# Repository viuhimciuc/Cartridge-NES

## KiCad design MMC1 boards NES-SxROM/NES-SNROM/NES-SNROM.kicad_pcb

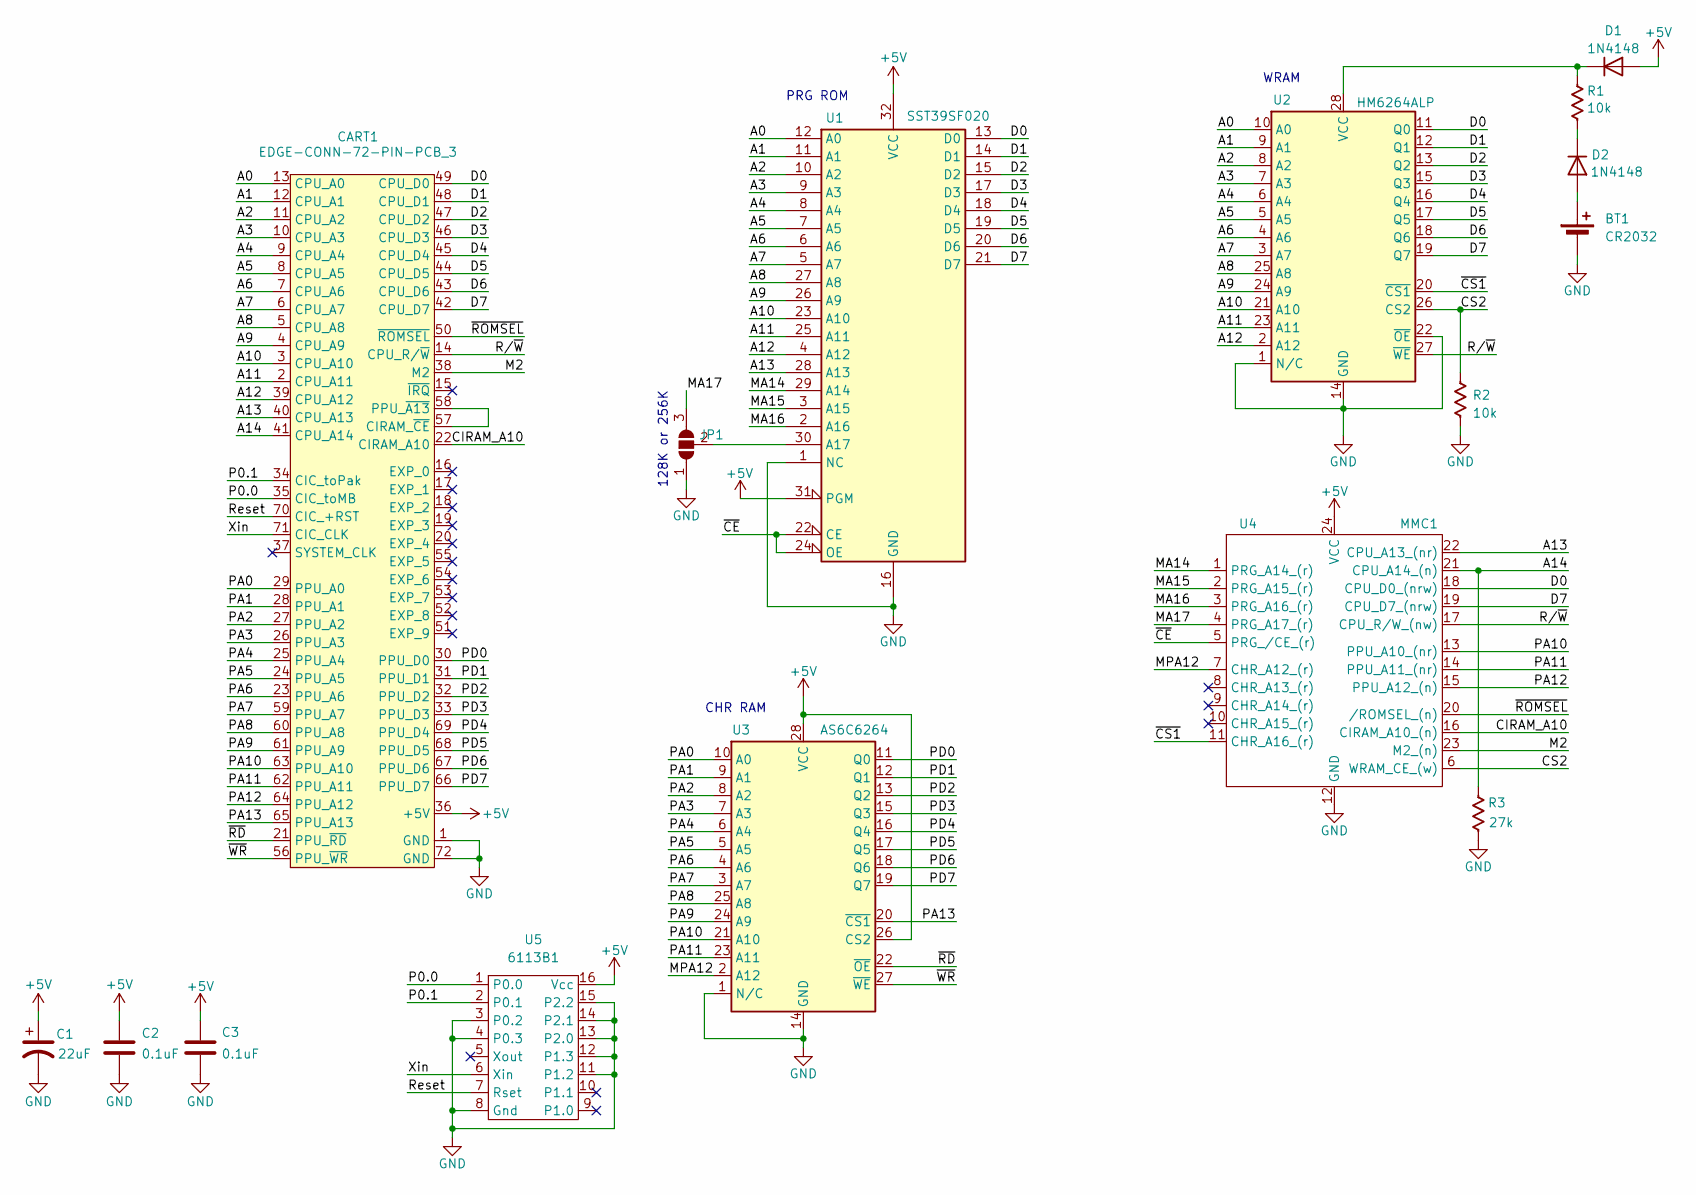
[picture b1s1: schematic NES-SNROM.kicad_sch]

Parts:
BT1: CR2032; Battery_Panasonic_CR2032-HFN_Horizontal_CircularHoles
C1: 22uF; CP_Radial_D4.0mm_P2.00mm
C2, C3: 0.1uF; C_Axial_P7.5mm_P2.50mm
CART1: EDGE-CONN-72-PIN-PCB_3; PCB_3-CART-72-2.50-CONN
D1, D2: 1N4148; D_DO-35_SOD27_P7.62mm_Horizontal
JP1: SolderJumper_3_Open; SolderJumper-3_P1.3mm_Open_RoundedPad1.0x1.5mm_NumberLabels
R1, R2: 10k; R_Axial_DIN0204_L3.6mm_D1.6mm_P5.08mm_Horizontal
R3: 27k; R_Axial_DIN0204_L3.6mm_D1.6mm_P5.08mm_Horizontal
U1: SST39SF020; DIP-32_W15.24mm
U2: HM6264ALP; DIP-28_W15.24mm
U3: AS6C6264; DIP-28_W15.24mm
U4: MMC1; DIP-24_W7.62mm_Pads_1.78mm
U5: 6113B1; DIP-16_W7.62mm

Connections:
+5V: C1.1, C2.1, C3.1, CART1.36 (+5V), D1.2 (A), U1.31 (PGM), U1.32 (VCC), U3.26 (CS2), U3.28 (VCC), U4.24 (VCC), U5.16 (Vcc)
/A0: CART1.13 (CPU_A0), U1.12 (A0), U2.10 (A0)
/A1: CART1.12 (CPU_A1), U1.11 (A1), U2.9 (A1)
/A2: CART1.11 (CPU_A2), U1.10 (A2), U2.8 (A2)
/A3: CART1.10 (CPU_A3), U1.9 (A3), U2.7 (A3)
/A4: CART1.9 (CPU_A4), U1.8 (A4), U2.6 (A4)
/A5: CART1.8 (CPU_A5), U1.7 (A5), U2.5 (A5)
/A6: CART1.7 (CPU_A6), U1.6 (A6), U2.4 (A6)
/A7: CART1.6 (CPU_A7), U1.5 (A7), U2.3 (A7)
/A8: CART1.5 (CPU_A8), U1.27 (A8), U2.25 (A8)
/A9: CART1.4 (CPU_A9), U1.26 (A9), U2.24 (A9)
/A10: CART1.3 (CPU_A10), U1.23 (A10), U2.21 (A10)
/A11: CART1.2 (CPU_A11), U1.25 (A11), U2.23 (A11)
/A12: CART1.39 (CPU_A12), U1.4 (A12), U2.2 (A12)
/A13: CART1.40 (CPU_A13), U1.28 (A13), U4.22 (CPU_A13_(nr))
/A14: CART1.41 (CPU_A14), R3.1, U4.21 (CPU_A14_(n))
/CIRAM_A10: CART1.22 (CIRAM_A10), U4.16 (CIRAM_A10_(n))
/CS2: R2.1, U2.26 (CS2), U4.6 (WRAM_CE_(w))
/D0: CART1.49 (CPU_D0), U1.13 (D0), U2.11 (Q0), U4.18 (CPU_D0_(nrw))
/D1: CART1.48 (CPU_D1), U1.14 (D1), U2.12 (Q1)
/D2: CART1.47 (CPU_D2), U1.15 (D2), U2.13 (Q2)
/D3: CART1.46 (CPU_D3), U1.17 (D3), U2.15 (Q3)
/D4: CART1.45 (CPU_D4), U1.18 (D4), U2.16 (Q4)
/D5: CART1.44 (CPU_D5), U1.19 (D5), U2.17 (Q5)
/D6: CART1.43 (CPU_D6), U1.20 (D6), U2.18 (Q6)
/D7: CART1.42 (CPU_D7), U1.21 (D7), U2.19 (Q7), U4.19 (CPU_D7_(nrw))
/M2: CART1.38 (M2), U4.23 (M2_(n))
/MA14: U1.29 (A14), U4.1 (PRG_A14_(r))
/MA15: U1.3 (A15), U4.2 (PRG_A15_(r))
/MA16: U1.2 (A16), U4.3 (PRG_A16_(r))
/MA17: JP1.3 (B), U4.4 (PRG_A17_(r))
/MPA12: U3.2 (A12), U4.7 (CHR_A12_(r))
/P0.0: CART1.35 (CIC_toMB), U5.1 (P0.0)
/P0.1: CART1.34 (CIC_toPak), U5.2 (P0.1)
/PA0: CART1.29 (PPU_A0), U3.10 (A0)
/PA1: CART1.28 (PPU_A1), U3.9 (A1)
/PA2: CART1.27 (PPU_A2), U3.8 (A2)
/PA3: CART1.26 (PPU_A3), U3.7 (A3)
/PA4: CART1.25 (PPU_A4), U3.6 (A4)
/PA5: CART1.24 (PPU_A5), U3.5 (A5)
/PA6: CART1.23 (PPU_A6), U3.4 (A6)
/PA7: CART1.59 (PPU_A7), U3.3 (A7)
/PA8: CART1.60 (PPU_A8), U3.25 (A8)
/PA9: CART1.61 (PPU_A9), U3.24 (A9)
/PA10: CART1.63 (PPU_A10), U3.21 (A10), U4.13 (PPU_A10_(nr))
/PA11: CART1.62 (PPU_A11), U3.23 (A11), U4.14 (PPU_A11_(nr))
/PA12: CART1.64 (PPU_A12), U4.15 (PPU_A12_(n))
/PA13: CART1.65 (PPU_A13), U3.20 (~CS1)
/PD0: CART1.30 (PPU_D0), U3.11 (Q0)
/PD1: CART1.31 (PPU_D1), U3.12 (Q1)
/PD2: CART1.32 (PPU_D2), U3.13 (Q2)
/PD3: CART1.33 (PPU_D3), U3.15 (Q3)
/PD4: CART1.69 (PPU_D4), U3.16 (Q4)
/PD5: CART1.68 (PPU_D5), U3.17 (Q5)
/PD6: CART1.67 (PPU_D6), U3.18 (Q6)
/PD7: CART1.66 (PPU_D7), U3.19 (Q7)
/Reset: CART1.70 (CIC_+RST), U5.7 (Rset)
/R/~W: CART1.14 (CPU_R/~W), U2.27 (~WE), U4.17 (CPU_R/W_(nw))
/Xin: CART1.71 (CIC_CLK), U5.6 (Xin)
/~CE: U1.22 (CE), U1.24 (OE), U4.5 (PRG_/CE_(r))
/~CS1: U2.20 (~CS1), U4.11 (CHR_A16_(r))
/~RD: CART1.21 (PPU_~RD), U3.22 (~OE)
/~ROMSEL: CART1.50 (~ROMSEL), U4.20 (/ROMSEL_(n))
/~WR: CART1.56 (PPU_~WR), U3.27 (~WE)
GND: BT1.2 (-), C1.2, C2.2, C3.2, CART1.1 (GND), CART1.72 (GND), JP1.1 (A), R2.2, R3.2, U1.1 (NC), U1.16 (GND), U2.1 (N/C), U2.14 (GND), U2.22 (~OE), U3.1 (N/C), U3.14 (GND), U4.12 (GND), U5.3 (P0.2), U5.4 (P0.3), U5.8 (Gnd), U5.11 (P1.2), U5.12 (P1.3), U5.13 (P2.0), U5.14 (P2.1), U5.15 (P2.2)
unnamed: BT1.1 (+), D2.2 (A)
unnamed: CART1.57 (CIRAM_~CE), CART1.58 (PPU_~A13)
unnamed: D1.1 (K), R1.1, U2.28 (VCC)
unnamed: D2.1 (K), R1.2
unnamed: JP1.2 (C), U1.30 (A17)

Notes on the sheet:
PRG ROM
WRAM
128K or 256K
CHR RAM

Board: 2 copper layers, 16 parts (1 on the bottom side), 70 nets, no tracks yet.

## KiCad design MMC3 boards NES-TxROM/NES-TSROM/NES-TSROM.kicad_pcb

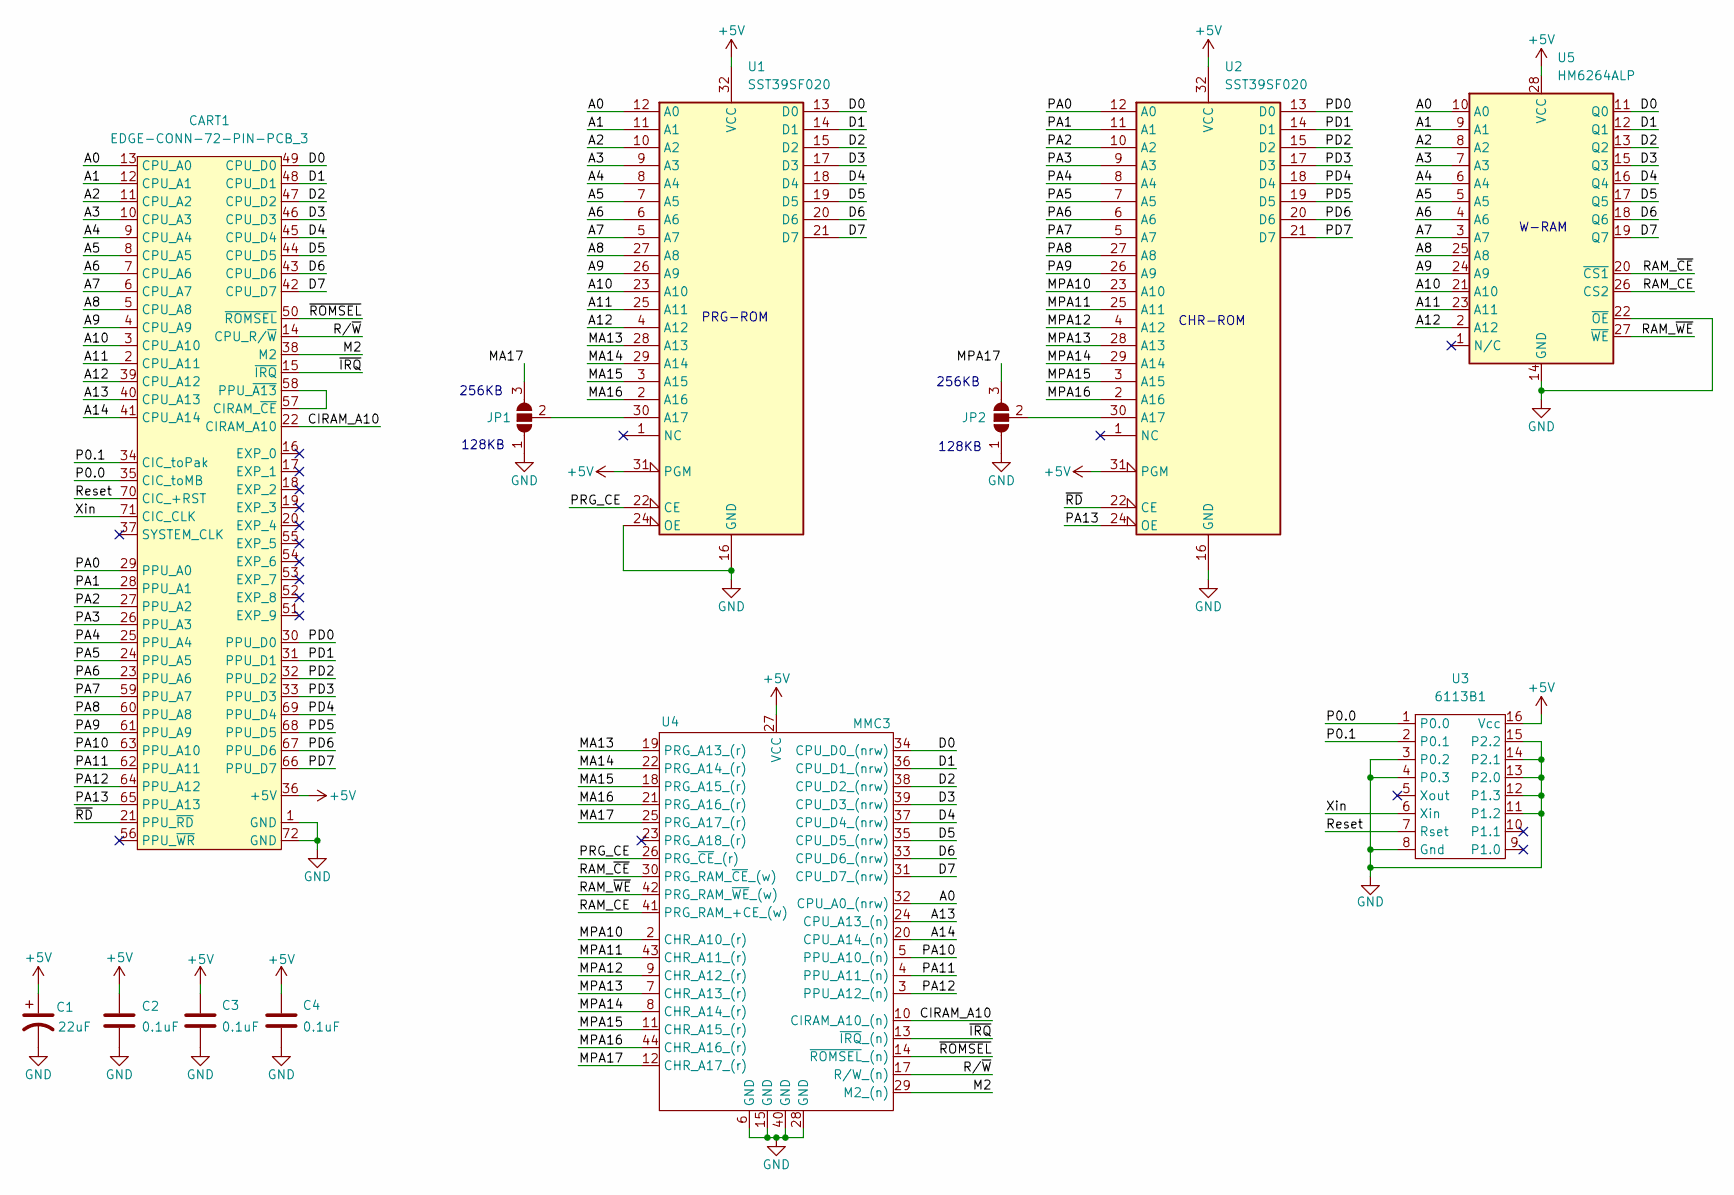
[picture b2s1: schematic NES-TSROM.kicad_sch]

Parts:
C1: 22uF; CP_Radial_D4.0mm_P2.00mm
C2, C3, C4: 0.1uF; C_Axial_P7.5mm_P2.50mm
CART1: EDGE-CONN-72-PIN-PCB_3; PCB_3-CART-72-2.50-CONN
JP1, JP2: SolderJumper_3_Open; SolderJumper-3_P1.3mm_Open_RoundedPad1.0x1.5mm_NumberLabels
U1, U2: SST39SF020; DIP-32_W15.24mm
U3: 6113B1; DIP-16_W7.62mm
U4: MMC3; MMC3_TQFP-44
U5: HM6264ALP; DIP-28_W15.24mm

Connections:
+5V: C1.1, C2.1, C3.1, C4.1, CART1.36 (+5V), U1.31 (PGM), U1.32 (VCC), U2.31 (PGM), U2.32 (VCC), U3.16 (Vcc), U4.27 (VCC), U5.28 (VCC)
/A0: CART1.13 (CPU_A0), U1.12 (A0), U4.32 (CPU_A0_(nrw)), U5.10 (A0)
/A1: CART1.12 (CPU_A1), U1.11 (A1), U5.9 (A1)
/A2: CART1.11 (CPU_A2), U1.10 (A2), U5.8 (A2)
/A3: CART1.10 (CPU_A3), U1.9 (A3), U5.7 (A3)
/A4: CART1.9 (CPU_A4), U1.8 (A4), U5.6 (A4)
/A5: CART1.8 (CPU_A5), U1.7 (A5), U5.5 (A5)
/A6: CART1.7 (CPU_A6), U1.6 (A6), U5.4 (A6)
/A7: CART1.6 (CPU_A7), U1.5 (A7), U5.3 (A7)
/A8: CART1.5 (CPU_A8), U1.27 (A8), U5.25 (A8)
/A9: CART1.4 (CPU_A9), U1.26 (A9), U5.24 (A9)
/A10: CART1.3 (CPU_A10), U1.23 (A10), U5.21 (A10)
/A11: CART1.2 (CPU_A11), U1.25 (A11), U5.23 (A11)
/A12: CART1.39 (CPU_A12), U1.4 (A12), U5.2 (A12)
/A13: CART1.40 (CPU_A13), U4.24 (CPU_A13_(n))
/A14: CART1.41 (CPU_A14), U4.20 (CPU_A14_(n))
/CIRAM_A10: CART1.22 (CIRAM_A10), U4.10 (CIRAM_A10_(n))
/D0: CART1.49 (CPU_D0), U1.13 (D0), U4.34 (CPU_D0_(nrw)), U5.11 (Q0)
/D1: CART1.48 (CPU_D1), U1.14 (D1), U4.36 (CPU_D1_(nrw)), U5.12 (Q1)
/D2: CART1.47 (CPU_D2), U1.15 (D2), U4.38 (CPU_D2_(nrw)), U5.13 (Q2)
/D3: CART1.46 (CPU_D3), U1.17 (D3), U4.39 (CPU_D3_(nrw)), U5.15 (Q3)
/D4: CART1.45 (CPU_D4), U1.18 (D4), U4.37 (CPU_D4_(nrw)), U5.16 (Q4)
/D5: CART1.44 (CPU_D5), U1.19 (D5), U4.35 (CPU_D5_(nrw)), U5.17 (Q5)
/D6: CART1.43 (CPU_D6), U1.20 (D6), U4.33 (CPU_D6_(nrw)), U5.18 (Q6)
/D7: CART1.42 (CPU_D7), U1.21 (D7), U4.31 (CPU_D7_(nrw)), U5.19 (Q7)
/M2: CART1.38 (M2), U4.29 (M2_(n))
/MA13: U1.28 (A13), U4.19 (PRG_A13_(r))
/MA14: U1.29 (A14), U4.22 (PRG_A14_(r))
/MA15: U1.3 (A15), U4.18 (PRG_A15_(r))
/MA16: U1.2 (A16), U4.21 (PRG_A16_(r))
/MA17: JP1.3 (B), U4.25 (PRG_A17_(r))
/MPA10: U2.23 (A10), U4.2 (CHR_A10_(r))
/MPA11: U2.25 (A11), U4.43 (CHR_A11_(r))
/MPA12: U2.4 (A12), U4.9 (CHR_A12_(r))
/MPA13: U2.28 (A13), U4.7 (CHR_A13_(r))
/MPA14: U2.29 (A14), U4.8 (CHR_A14_(r))
/MPA15: U2.3 (A15), U4.11 (CHR_A15_(r))
/MPA16: U2.2 (A16), U4.44 (CHR_A16_(r))
/MPA17: JP2.3 (B), U4.12 (CHR_A17_(r))
/P0.0: CART1.35 (CIC_toMB), U3.1 (P0.0)
/P0.1: CART1.34 (CIC_toPak), U3.2 (P0.1)
/PA0: CART1.29 (PPU_A0), U2.12 (A0)
/PA1: CART1.28 (PPU_A1), U2.11 (A1)
/PA2: CART1.27 (PPU_A2), U2.10 (A2)
/PA3: CART1.26 (PPU_A3), U2.9 (A3)
/PA4: CART1.25 (PPU_A4), U2.8 (A4)
/PA5: CART1.24 (PPU_A5), U2.7 (A5)
/PA6: CART1.23 (PPU_A6), U2.6 (A6)
/PA7: CART1.59 (PPU_A7), U2.5 (A7)
/PA8: CART1.60 (PPU_A8), U2.27 (A8)
/PA9: CART1.61 (PPU_A9), U2.26 (A9)
/PA10: CART1.63 (PPU_A10), U4.5 (PPU_A10_(n))
/PA11: CART1.62 (PPU_A11), U4.4 (PPU_A11_(n))
/PA12: CART1.64 (PPU_A12), U4.3 (PPU_A12_(n))
/PA13: CART1.65 (PPU_A13), U2.24 (OE)
/PD0: CART1.30 (PPU_D0), U2.13 (D0)
/PD1: CART1.31 (PPU_D1), U2.14 (D1)
/PD2: CART1.32 (PPU_D2), U2.15 (D2)
/PD3: CART1.33 (PPU_D3), U2.17 (D3)
/PD4: CART1.69 (PPU_D4), U2.18 (D4)
/PD5: CART1.68 (PPU_D5), U2.19 (D5)
/PD6: CART1.67 (PPU_D6), U2.20 (D6)
/PD7: CART1.66 (PPU_D7), U2.21 (D7)
/PRG_CE: U1.22 (CE), U4.26 (PRG_~CE_(r))
/RAM_CE: U4.41 (PRG_RAM_+CE_(w)), U5.26 (CS2)
/RAM_~CE: U4.30 (PRG_RAM_~CE_(w)), U5.20 (~CS1)
/RAM_~WE: U4.42 (PRG_RAM_~WE_(w)), U5.27 (~WE)
/Reset: CART1.70 (CIC_+RST), U3.7 (Rset)
/R/~W: CART1.14 (CPU_R/~W), U4.17 (R/W_(n))
/Xin: CART1.71 (CIC_CLK), U3.6 (Xin)
/~IRQ: CART1.15 (~IRQ), U4.13 (~IRQ_(n))
/~RD: CART1.21 (PPU_~RD), U2.22 (CE)
/~ROMSEL: CART1.50 (~ROMSEL), U4.14 (~ROMSEL_(n))
GND: C1.2, C2.2, C3.2, C4.2, CART1.1 (GND), CART1.72 (GND), JP1.1 (A), JP2.1 (A), U1.16 (GND), U1.24 (OE), U2.16 (GND), U3.3 (P0.2), U3.4 (P0.3), U3.8 (Gnd), U3.11 (P1.2), U3.12 (P1.3), U3.13 (P2.0), U3.14 (P2.1), U3.15 (P2.2), U4.6 (GND), U4.15 (GND), U4.28 (GND), U4.40 (GND), U5.14 (GND), U5.22 (~OE)
unnamed: CART1.57 (CIRAM_~CE), CART1.58 (PPU_~A13)
unnamed: JP1.2 (C), U1.30 (A17)
unnamed: JP2.2 (C), U2.30 (A17)

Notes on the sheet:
W-RAM
CHR-ROM
256KB
128KB
PRG-ROM

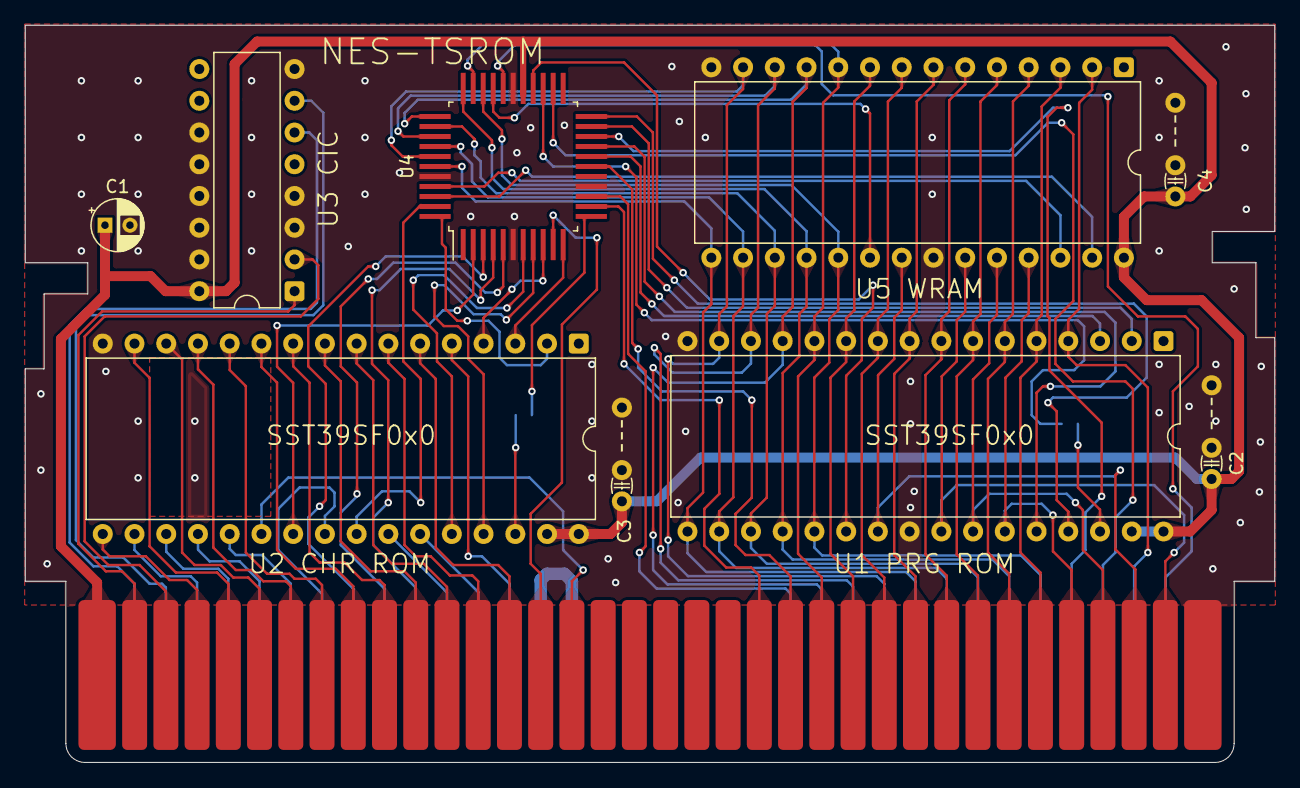
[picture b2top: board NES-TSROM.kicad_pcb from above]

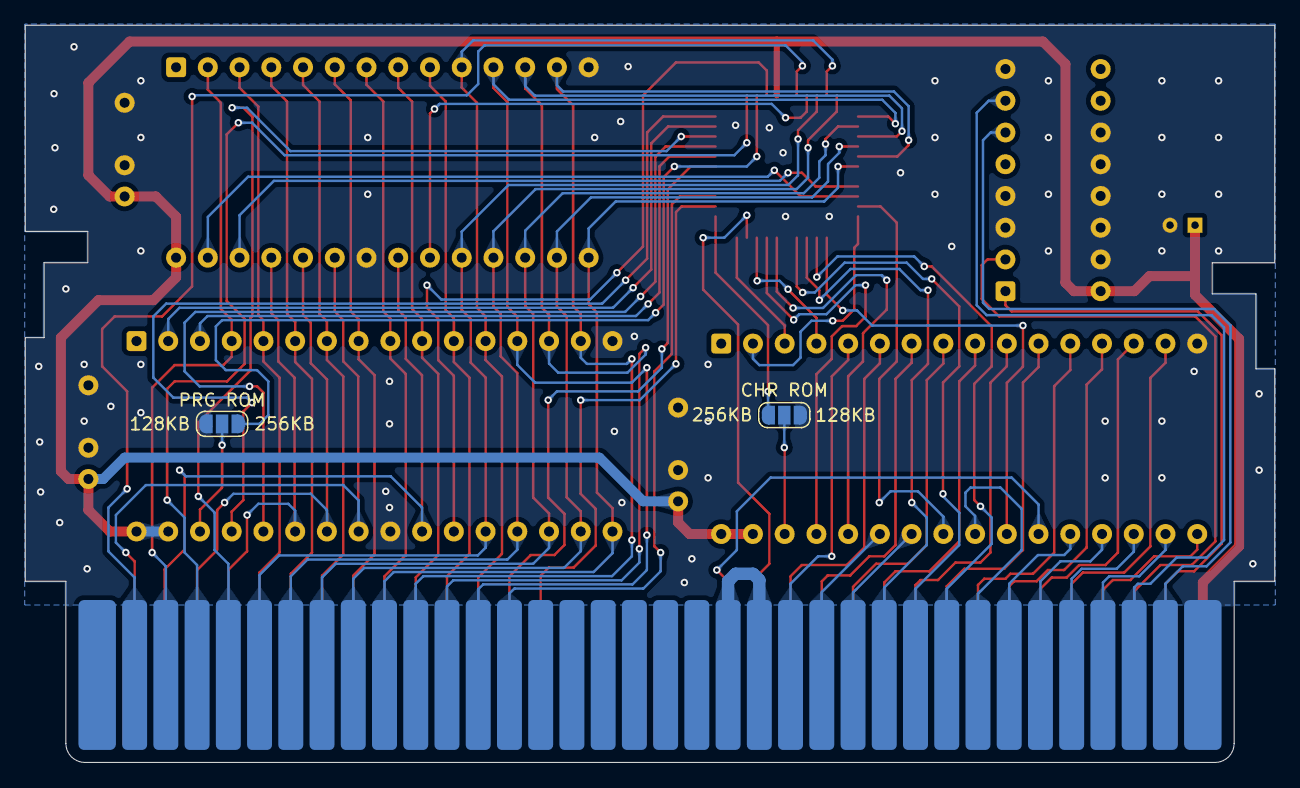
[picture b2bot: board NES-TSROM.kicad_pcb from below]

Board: 2 copper layers, 100.0 x 59.0 mm, 12 parts (2 on the bottom side), 77 nets.

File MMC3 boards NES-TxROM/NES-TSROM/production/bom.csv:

Designator,Footprint,Quantity,Value,LCSC Part #
C1,CP_Radial_D4.0mm_P2.00mm,1,22uF,
"C2, C3, C4",C_Axial_P7.5mm_P2.50mm,3,0.1uF,
CART1,PCB_3-CART-72-2.50-CONN,1,EDGE-CONN-72-PIN-PCB_3,
"U1, U2",DIP-32_W15.24mm,2,SST39SF020,
U3,DIP-16_W7.62mm,1,6113B1,
U4,MMC3_TQFP-44,1,MMC3,
U5,DIP-28_W15.24mm,1,HM6264ALP,
